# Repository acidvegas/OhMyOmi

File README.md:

# OhMyOmi

A DIY approach to building your own [Omi](https://www.omi.me) wearable for less than the cost of buying one. It is a small round pendant that records your conversations with two MEMS microphones, saves them to on-board flash and syncs to your phone over Bluetooth later, or streams live. The whole board is generated from Python scripts, autorouted with Freerouting and ready to order from JLCPCB with assembly.

| Parts side *(faces into the case)* | Front face *(against the case front)* |
| :---: | :---: |
|  |  |

## Board

- Ø26 mm round, 6 layers, 0.8 mm thick, ENIG
- Every assembled part on one side *(JLCPCB Economic PCBA)*. The blank side sits flat against the inside of the case front.
- Mics listen through 0.8 mm holes in the board and the RGB LED shines through a slot, so no light pipe is needed
- Pendant size with a case is about Ø28.9 x 12.3 mm

| Part                | What it does                                                 |
|---------------------|--------------------------------------------------------------|
| ISP1807-LR-RS       | nRF52840 Bluetooth module with built-in antenna and crystals |
| 2x IM73D122V01      | Infineon PDM microphones, 73 dB SNR, stereo on one bus       |
| MKDV4GCL-ABB        | 512 MB SLC SD NAND over SPI, power switched by a P-MOSFET    |
| LIS2DW12            | Accelerometer for tap controls and motion wake               |
| MCP73832            | LiPo charger, 66 mA                                          |
| TPS7A0233           | 3.3 V LDO, 25 nA quiescent                                   |
| USBLC6-2P6          | ESD protection on USB                                        |
| HRO TYPE-C-31-M-12  | USB-C for charging and USB data                              |
| MHT151RGBCT         | Reverse mount RGB LED                                        |
| DMG1012T + RB521S30 | Vibration motor driver                                       |

The battery is a 150 mAh CP1654 cell with wire leads soldered to the B+ and B- pads. A coin vibration motor solders to M+ and M-. Four test pads on the front face carry SWDIO, SWDCLK, 3V3 and GND for programming.

## Ordering

Upload these from `pcb/jlcpcb/` to JLCPCB:

- `omi-gerbers.zip` for the board
- `omi-bom.csv` and `omi-cpl.csv` for assembly

Check the part rotations in the JLCPCB placement preview before paying, especially LED1, both mics, U4, U5, U6, Q1, Q2, D1 and J1. Cost for 5 boards with 2 assembled is about $120 before shipping, the battery and the motor. The ISP1807 comes through JLCPCB Global Sourcing.

## Firmware notes

The firmware is not written yet. The board depends on these settings:

- PDM clock 1.280 MHz with ratio 80 *(16 kHz)*. The nRF default of 1.032 MHz falls between the mic's power modes and will not work.
- Stereo PDM, MK1 on the falling edge and MK2 on the rising edge
- LED pins P0.13, P0.17 and P0.14 in high drive mode
- Drive P0.30 low to power the SD NAND, and float its SPI pins before turning it off
- Charge status on P0.31 *(low while charging)*
- Battery voltage on AIN4 through a 1M/1M divider, TACQ 40 us
- Enable the nRF DC/DC *(DCDCEN)*
- Compress audio before saving *(Opus)*. Raw 16 kHz stereo fills 512 MB in about 2 hours.
- Use a watchdog. There is no reset button.

## Building

Needs KiCad 9 *(pcbnew Python and kicad-cli)* and Flask for the preview.

```
cd pcb
python3 gen_lib.py                         # footprints, symbols, schematic
python3 build_pcb.py place                 # unrouted board with zones and keepouts
cp omi.kicad_pcb omi_unrouted.kicad_pcb
./flow.sh                                  # autoroute, import, pours, fixups, DRC
./rebuild.sh                               # redo pours, fixups and DRC on the last route without re-routing
python3 outputs.py                         # gerbers, BOM, CPL, renders, 3D model
python3 compare.py                         # size comparison render
python3 summary.py                         # prices, stock and cost for the preview
```

`flow.sh` runs Freerouting 2.5.0 from `tools/` with its own Java 25 runtime, inside `sudo unshare -n` so it has no network access. `tools/` is not tracked. Put `freerouting-2.5.0.jar` and a Java 25 JRE back there to re-route.

## Previews

- `pcb/preview/app.py` serves the board preview *(layers, cost, parts, 3D view at `/3d`)* on port 20005
- `app.py` serves the original dev-board wiring preview on port 20004

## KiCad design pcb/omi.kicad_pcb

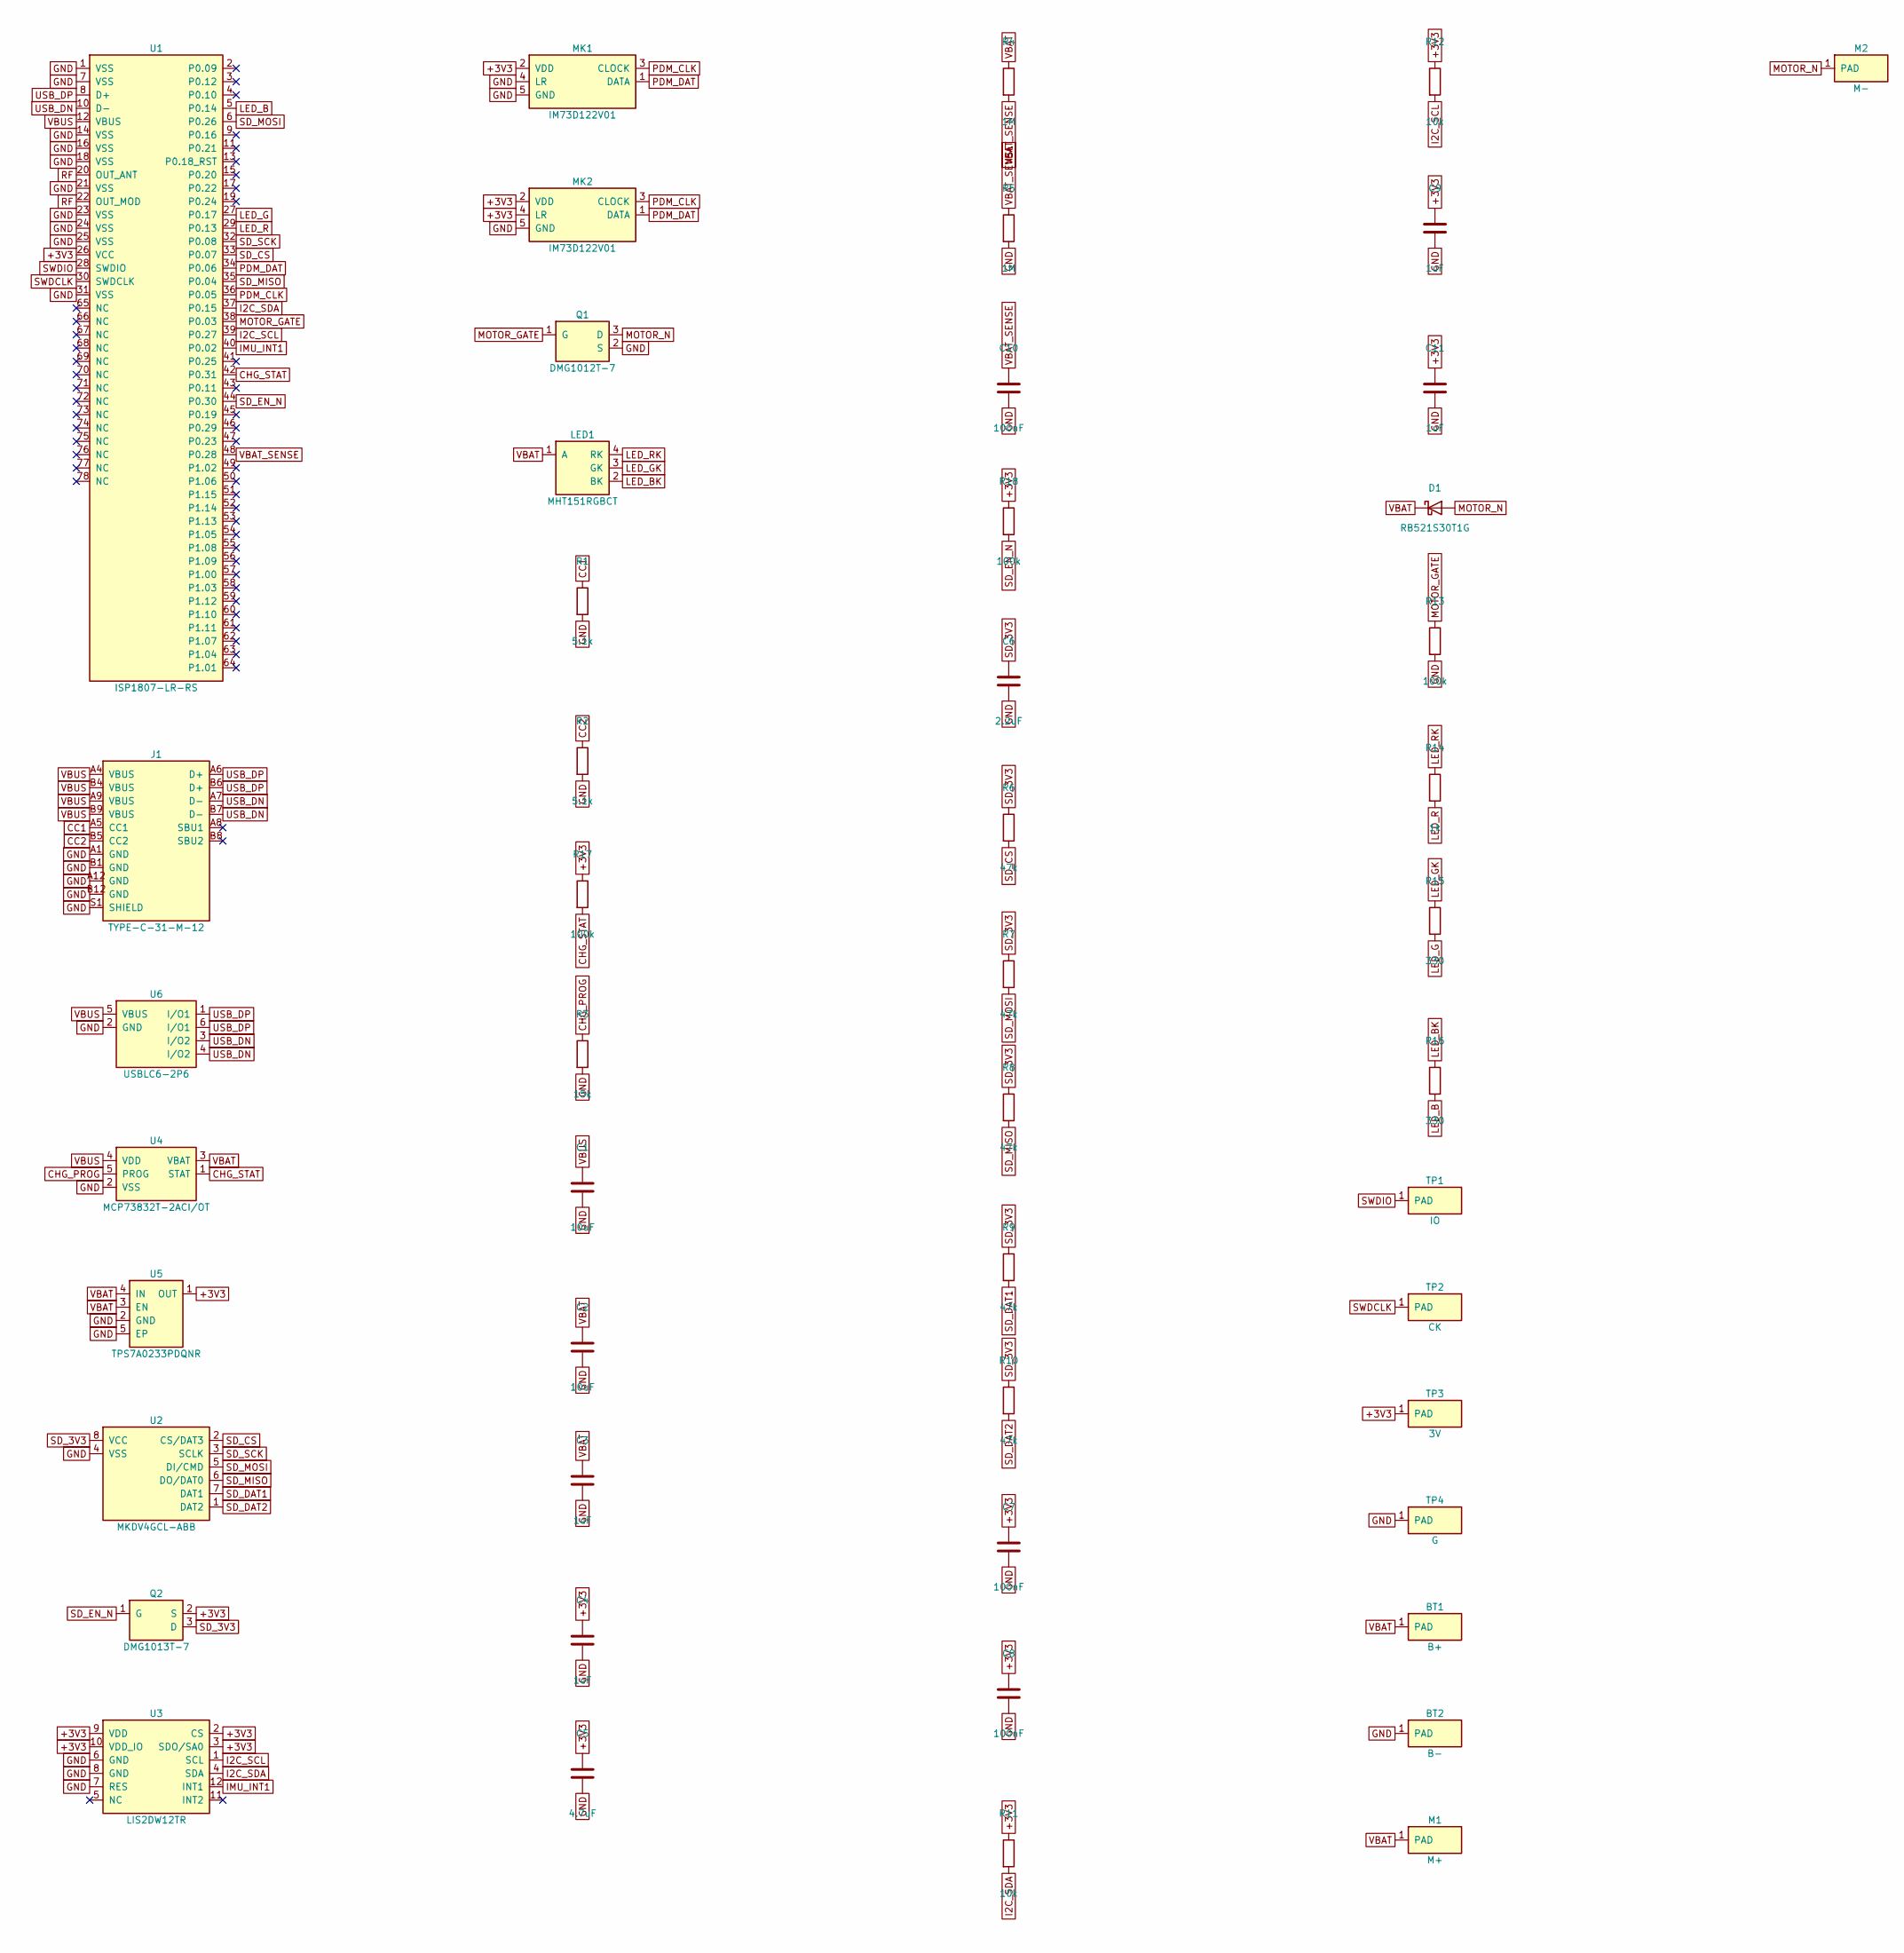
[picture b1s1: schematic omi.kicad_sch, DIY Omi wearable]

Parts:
BT1: B+; TestPoint_Pad_1.0x1.0mm
BT2: B-; TestPoint_Pad_1.0x1.0mm
C1: 10uF; C_0603_1608Metric; LCSC C19702
C2: 10uF; C_0402_1005Metric; LCSC C15525
C3, C4, C9, C11: 1uF; C_0402_1005Metric; LCSC C52923
C5: 4.7uF; C_0402_1005Metric; LCSC C23733
C6: 2.2uF; C_0402_1005Metric; LCSC C12530
C7, C8, C10: 100nF; C_0402_1005Metric; LCSC C1525
D1: RB521S30T1G; D_SOD-523; LCSC C145179
J1: TYPE-C-31-M-12; USB_C_Receptacle_HRO_TYPE-C-31-M-12; LCSC C165948
LED1: MHT151RGBCT; LED_RGB_REV_1206; LCSC C409782
M1: M+; TestPoint_Pad_1.0x1.0mm
M2: M-; TestPoint_Pad_1.0x1.0mm
MK1, MK2: IM73D122V01; IM73D122_LGA5_4x3; LCSC C5563886
Q1: DMG1012T-7; SOT-523; LCSC C20512
Q2: DMG1013T-7; SOT-523; LCSC C96676
R1, R2: 5.1k; R_0402_1005Metric; LCSC C25905
R3: 15k; R_0402_1005Metric; LCSC C25756
R4, R5: 1M; R_0402_1005Metric; LCSC C26083
R6, R7, R8, R9, R10: 47k; R_0402_1005Metric; LCSC C25792
R11, R12: 10k; R_0402_1005Metric; LCSC C25744
R13, R17, R18: 100k; R_0402_1005Metric; LCSC C25741
R14: 1k; R_0402_1005Metric; LCSC C11702
R15, R16: 330; R_0402_1005Metric; LCSC C25104
TP1: IO; TestPoint_Pad_D1.0mm
TP2: CK; TestPoint_Pad_D1.0mm
TP3: 3V; TestPoint_Pad_D1.0mm
TP4: G; TestPoint_Pad_D1.0mm
U1: ISP1807-LR-RS; ISP1807; LCSC C5264268
U2: MKDV4GCL-ABB; SDNAND_LGA8_8x6; LCSC C7500178
U3: LIS2DW12TR; LGA-12_2x2mm_P0.5mm; LCSC C189624
U4: MCP73832T-2ACI/OT; SOT-23-5; LCSC C38066
U5: TPS7A0233PDQNR; Texas_X2SON-4_1x1mm_P0.65mm; LCSC C2860046
U6: USBLC6-2P6; SOT-666; LCSC C15999

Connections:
+3V3: C4.1, C5.1, C7.1, C8.1, C9.1, C11.1, MK1.2 (VDD), MK2.2 (VDD), MK2.4 (LR), Q2.2 (S), R11.1, R12.1, R17.1, R18.1, TP3.1, U1.26 (VCC), U3.2 (CS), U3.3 (SDO/SA0), U3.9 (VDD), U3.10 (VDD_IO), U5.1 (OUT)
CC1: J1.A5 (CC1), R1.1
CC2: J1.B5 (CC2), R2.1
CHG_PROG: R3.1, U4.5 (PROG)
CHG_STAT: R17.2, U1.42 (P0.31), U4.1 (STAT)
GND: BT2.1, C1.2, C2.2, C3.2, C4.2, C5.2, C6.2, C7.2, C8.2, C9.2, C10.2, C11.2, J1.A1 (GND), J1.A12 (GND), J1.B1 (GND), J1.B12 (GND), J1.S1 (SHIELD), MK1.4 (LR), MK1.5 (GND), MK2.5 (GND), Q1.2 (S), R1.2, R2.2, R3.2, R5.2, R13.2, TP4.1, U1.1 (VSS), U1.7 (VSS), U1.14 (VSS), U1.16 (VSS), U1.18 (VSS), U1.21 (VSS), U1.23 (VSS), U1.24 (VSS), U1.25 (VSS), U1.31 (VSS), U2.4 (VSS), U3.6 (GND), U3.7 (RES), U3.8 (GND), U4.2 (VSS), U5.2 (GND), U5.5 (EP), U6.2 (GND)
I2C_SCL: R12.2, U1.39 (P0.27), U3.1 (SCL)
I2C_SDA: R11.2, U1.37 (P0.15), U3.4 (SDA)
IMU_INT1: U1.40 (P0.02), U3.12 (INT1)
LED_B: R16.2, U1.5 (P0.14)
LED_BK: LED1.2 (BK), R16.1
LED_G: R15.2, U1.27 (P0.17)
LED_GK: LED1.3 (GK), R15.1
LED_R: R14.2, U1.29 (P0.13)
LED_RK: LED1.4 (RK), R14.1
MOTOR_GATE: Q1.1 (G), R13.1, U1.38 (P0.03)
MOTOR_N: D1.2 (A), M2.1, Q1.3 (D)
PDM_CLK: MK1.3 (CLOCK), MK2.3 (CLOCK), U1.36 (P0.05)
PDM_DAT: MK1.1 (DATA), MK2.1 (DATA), U1.34 (P0.06)
RF: U1.20 (OUT_ANT), U1.22 (OUT_MOD)
SD_3V3: C6.1, Q2.3 (D), R6.1, R7.1, R8.1, R9.1, R10.1, U2.8 (VCC)
SD_CS: R6.2, U1.33 (P0.07), U2.2 (CS/DAT3)
SD_DAT1: R9.2, U2.7 (DAT1)
SD_DAT2: R10.2, U2.1 (DAT2)
SD_EN_N: Q2.1 (G), R18.2, U1.44 (P0.30)
SD_MISO: R8.2, U1.35 (P0.04), U2.6 (DO/DAT0)
SD_MOSI: R7.2, U1.6 (P0.26), U2.5 (DI/CMD)
SD_SCK: U1.32 (P0.08), U2.3 (SCLK)
SWDCLK: TP2.1, U1.30 (SWDCLK)
SWDIO: TP1.1, U1.28 (SWDIO)
USB_DN: J1.A7 (D-), J1.B7 (D-), U1.10 (D-), U6.3 (I/O2), U6.4 (I/O2)
USB_DP: J1.A6 (D+), J1.B6 (D+), U1.8 (D+), U6.1 (I/O1), U6.6 (I/O1)
VBAT: BT1.1, C2.1, C3.1, D1.1 (K), LED1.1 (A), M1.1, R4.1, U4.3 (VBAT), U5.3 (EN), U5.4 (IN)
VBAT_SENSE: C10.1, R4.2, R5.1, U1.48 (P0.28)
VBUS: C1.1, J1.A4 (VBUS), J1.A9 (VBUS), J1.B4 (VBUS), J1.B9 (VBUS), U1.12 (VBUS), U4.4 (VDD), U6.5 (VBUS)

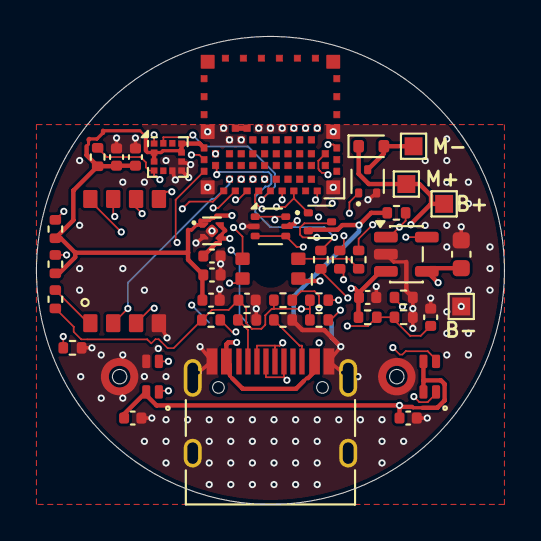
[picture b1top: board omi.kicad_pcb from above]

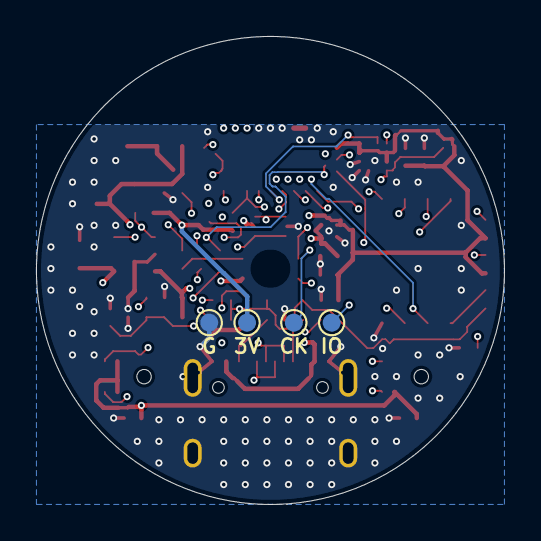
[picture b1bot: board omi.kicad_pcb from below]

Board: 6 copper layers, 26.0 x 26.0 mm, 50 parts (4 on the bottom side), 35 nets.

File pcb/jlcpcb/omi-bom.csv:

Comment,Designator,Footprint,LCSC Part #
ISP1807-LR-RS,U1,ISP1807,C5264268
TYPE-C-31-M-12,J1,USB_C_Receptacle_HRO_TYPE-C-31-M-12,C165948
5.1k,"R1,R2",R_0402_1005Metric,C25905
USBLC6-2P6,U6,SOT-666,C15999
MCP73832T-2ACI/OT,U4,SOT-23-5,C38066
100k,"R17,R18,R13",R_0402_1005Metric,C25741
15k,R3,R_0402_1005Metric,C25756
10uF,C1,C_0603_1608Metric,C19702
10uF,C2,C_0402_1005Metric,C15525
TPS7A0233PDQNR,U5,Texas_X2SON-4_1x1mm_P0.65mm,C2860046
1uF,"C3,C4,C9,C11",C_0402_1005Metric,C52923
4.7uF,C5,C_0402_1005Metric,C23733
1M,"R4,R5",R_0402_1005Metric,C26083
100nF,"C10,C7,C8",C_0402_1005Metric,C1525
MKDV4GCL-ABB,U2,SDNAND_LGA8_8x6,C7500178
DMG1013T-7,Q2,SOT-523,C96676
2.2uF,C6,C_0402_1005Metric,C12530
47k,"R6,R7,R8,R9,R10",R_0402_1005Metric,C25792
LIS2DW12TR,U3,LGA-12_2x2mm_P0.5mm,C189624
10k,"R11,R12",R_0402_1005Metric,C25744
IM73D122V01,"MK1,MK2",IM73D122_LGA5_4x3,C5563886
DMG1012T-7,Q1,SOT-523,C20512
RB521S30T1G,D1,D_SOD-523,C145179
MHT151RGBCT,LED1,LED_RGB_REV_1206,C409782
1k,R14,R_0402_1005Metric,C11702
330,"R15,R16",R_0402_1005Metric,C25104

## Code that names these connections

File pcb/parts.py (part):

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		'32': 'SD_SCK', '6': 'SD_MOSI', '35': 'SD_MISO', '33': 'SD_CS',
		'37': 'I2C_SDA', '39': 'I2C_SCL', '40': 'IMU_INT1',
		'48': 'VBAT_SENSE', '38': 'MOTOR_GATE',
		'29': 'LED_R', '27': 'LED_G', '5': 'LED_B',  # high-drive capable pins (P0.13/P0.17/P0.14)
		'42': 'CHG_STAT', '44': 'SD_EN_N',  # static signals on low-frequency pins (P0.31/P0.30)
	}),

	# --- USB-C charging/data at the bottom edge, 5.1k CC pull-downs so any USB-C charger supplies 5V ---
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	dict(ref='R1', value='5.1k', sym='Device:R', fp='Resistor_SMD:R_0402_1005Metric', lcsc='C25905', pins={'1': 'CC1', '2': 'GND'}),
	dict(ref='R2', value='5.1k', sym='Device:R', fp='Resistor_SMD:R_0402_1005Metric', lcsc='C25905', pins={'1': 'CC2', '2': 'GND'}),
	# ESD clamp on D+/D-/VBUS (flow-through: pins 1/6 = I/O1, 3/4 = I/O2)
	dict(ref='U6', value='USBLC6-2P6', sym='omi:USBLC6', fp='Package_TO_SOT_SMD:SOT-666', lcsc='C15999', pins={'1': 'USB_DP', '6': 'USB_DP', '3': 'USB_DN', '4': 'USB_DN', '2': 'GND', '5': 'VBUS'}),

	# --- charger: MCP73832 (open-drain STAT), I = 1000V / RPROG -> 15k = 66mA (~0.5C for a 120-150mAh CP1654 cell) ---
	dict(ref='U4', value='MCP73832T-2ACI/OT', sym='omi:MCP73832', fp='Package_TO_SOT_SMD:SOT-23-5', lcsc='C38066', pins={'1': 'CHG_STAT', '2': 'GND', '3': 'VBAT', '4': 'VBUS', '5': 'CHG_PROG'}),
	dict(ref='R17', value='100k', sym='Device:R', fp='Resistor_SMD:R_0402_1005Metric', lcsc='C25741', pins={'1': '+3V3', '2': 'CHG_STAT'}),
	dict(ref='R3', value='15k', sym='Device:R', fp='Resistor_SMD:R_0402_1005Metric', lcsc='C25756', pins={'1': 'CHG_PROG', '2': 'GND'}),
	dict(ref='C1', value='10uF', sym='Device:C', fp='Capacitor_SMD:C_0603_1608Metric', lcsc='C19702', pins={'1': 'VBUS', '2': 'GND'}),
	dict(ref='C2', value='10uF', sym='Device:C', fp='Capacitor_SMD:C_0402_1005Metric', lcsc='C15525', pins={'1': 'VBAT', '2': 'GND'}),

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	dict(ref='C5', value='4.7uF', sym='Device:C', fp='Capacitor_SMD:C_0402_1005Metric', lcsc='C23733', pins={'1': '+3V3', '2': 'GND'}),

	# --- battery sense divider (VBAT/2 on P0.28 = AIN4, sample with TACQ = 40 us) ---
	dict(ref='R4', value='1M', sym='Device:R', fp='Resistor_SMD:R_0402_1005Metric', lcsc='C26083', pins={'1': 'VBAT', '2': 'VBAT_SENSE'}),
	dict(ref='R5', value='1M', sym='Device:R', fp='Resistor_SMD:R_0402_1005Metric', lcsc='C26083', pins={'1': 'VBAT_SENSE', '2': 'GND'}),
	dict(ref='C10', value='100nF', sym='Device:C', fp='Capacitor_SMD:C_0402_1005Metric', lcsc='C1525', pins={'1': 'VBAT_SENSE', '2': 'GND'}),

	# --- SD NAND 4 Gbit / 512 MB (SPI mode), on its own switched rail so standby drops ~50 uA -> 0 ---
	dict(ref='U2', value='MKDV4GCL-ABB', sym='omi:SDNAND', fp='omi:SDNAND_LGA8_8x6', lcsc='C7500178', pins={'1': 'SD_DAT2', '2': 'SD_CS', '3': 'SD_SCK', '4': 'GND', '5': 'SD_MOSI', '6': 'SD_MISO', '7': 'SD_DAT1', '8': 'SD_3V3'}),
	dict(ref='Q2', value='DMG1013T-7', sym='omi:PMOS_GSD', fp='Package_TO_SOT_SMD:SOT-523', lcsc='C96676', pins={'1': 'SD_EN_N', '2': '+3V3', '3': 'SD_3V3'}),
	dict(ref='R18', value='100k', sym='Device:R', fp='Resistor_SMD:R_0402_1005Metric', lcsc='C25741', pins={'1': '+3V3', '2': 'SD_EN_N'}),
	dict(ref='C6', value='2.2uF', sym='Device:C', fp='Capacitor_SMD:C_0402_1005Metric', lcsc='C12530', pins={'1': 'SD_3V3', '2': 'GND'}),
	dict(ref='R6', value='47k', sym='Device:R', fp='Resistor_SMD:R_0402_1005Metric', lcsc='C25792', pins={'1': 'SD_3V3', '2': 'SD_CS'}),
	dict(ref='R7', value='47k', sym='Device:R', fp='Resistor_SMD:R_0402_1005Metric', lcsc='C25792', pins={'1': 'SD_3V3', '2': 'SD_MOSI'}),
	dict(ref='R8', value='47k', sym='Device:R', fp='Resistor_SMD:R_0402_1005Metric', lcsc='C25792', pins={'1': 'SD_3V3', '2': 'SD_MISO'}),
	dict(ref='R9', value='47k', sym='Device:R', fp='Resistor_SMD:R_0402_1005Metric', lcsc='C25792', pins={'1': 'SD_3V3', '2': 'SD_DAT1'}),
	dict(ref='R10', value='47k', sym='Device:R', fp='Resistor_SMD:R_0402_1005Metric', lcsc='C25792', pins={'1': 'SD_3V3', '2': 'SD_DAT2'}),

	# --- accelerometer for motion wake (I2C, CS and SA0 tied high so their internal pull-ups draw nothing, addr 0x19) ---
	dict(ref='U3', value='LIS2DW12TR', sym='omi:LIS2DW12', fp='Package_LGA:LGA-12_2x2mm_P0.5mm', lcsc='C189624', pins={
		'1': 'I2C_SCL', '2': '+3V3', '3': '+3V3', '4': 'I2C_SDA', '5': None, '6': 'GND', '7': 'GND', '8': 'GND', '9': '+3V3', '10': '+3V3', '11': None, '12': 'IMU_INT1'}),
	dict(ref='C7', value='100nF', sym='Device:C', fp='Capacitor_SMD:C_0402_1005Metric', lcsc='C1525', pins={'1': '+3V3', '2': 'GND'}),
	dict(ref='C8', value='100nF', sym='Device:C', fp='Capacitor_SMD:C_0402_1005Metric', lcsc='C1525', pins={'1': '+3V3', '2': 'GND'}),
	dict(ref='R11', value='10k', sym='Device:R', fp='Resistor_SMD:R_0402_1005Metric', lcsc='C25744', pins={'1': '+3V3', '2': 'I2C_SDA'}),
	dict(ref='R12', value='10k', sym='Device:R', fp='Resistor_SMD:R_0402_1005Metric', lcsc='C25744', pins={'1': '+3V3', '2': 'I2C_SCL'}),

	# --- 2x bottom-port PDM mics on the component side, listening through 0.8 mm board holes straight out the front face; shared clock/data, LR selects the edge ---
	dict(ref='MK1', value='IM73D122V01', sym='omi:IM73D122', fp='omi:IM73D122_LGA5_4x3', lcsc='C5563886', pins={'1': 'PDM_DAT', '2': '+3V3', '3': 'PDM_CLK', '4': 'GND', '5': 'GND'}),
	dict(ref='MK2', value='IM73D122V01', sym='omi:IM73D122', fp='omi:IM73D122_LGA5_4x3', lcsc='C5563886', pins={'1': 'PDM_DAT', '2': '+3V3', '3': 'PDM_CLK', '4': '+3V3', '5': 'GND'}),
	dict(ref='C9', value='1uF', sym='Device:C', fp='Capacitor_SMD:C_0402_1005Metric', lcsc='C52923', pins={'1': '+3V3', '2': 'GND'}),
	dict(ref='C11', value='1uF', sym='Device:C', fp='Capacitor_SMD:C_0402_1005Metric', lcsc='C52923', pins={'1': '+3V3', '2': 'GND'}),

	# --- vibration motor driver (motor solders to M+ / M- pads) ---
	dict(ref='Q1', value='DMG1012T-7', sym='omi:NMOS_GSD', fp='Package_TO_SOT_SMD:SOT-523', lcsc='C20512', pins={'1': 'MOTOR_GATE', '2': 'GND', '3': 'MOTOR_N'}),
	dict(ref='D1', value='RB521S30T1G', sym='Device:D_Schottky', fp='Diode_SMD:D_SOD-523', lcsc='C145179', pins={'1': 'VBAT', '2': 'MOTOR_N'}),
	dict(ref='R13', value='100k', sym='Device:R', fp='Resistor_SMD:R_0402_1005Metric', lcsc='C25741', pins={'1': 'MOTOR_GATE', '2': 'GND'}),

	# --- RGB LED, reverse mount: sits on the inner side and shines out through a slot in the board (common anode on VBAT, GPIO sinks) ---
	dict(ref='LED1', value='MHT151RGBCT', sym='omi:LED_RGB_CA', fp='omi:LED_RGB_REV_1206', lcsc='C409782', pins={'1': 'VBAT', '2': 'LED_BK', '3': 'LED_GK', '4': 'LED_RK'}),
	dict(ref='R14', value='1k', sym='Device:R', fp='Resistor_SMD:R_0402_1005Metric', lcsc='C11702', pins={'1': 'LED_RK', '2': 'LED_R'}),
	dict(ref='R15', value='330', sym='Device:R', fp='Resistor_SMD:R_0402_1005Metric', lcsc='C25104', pins={'1': 'LED_GK', '2': 'LED_G'}),
	dict(ref='R16', value='330', sym='Device:R', fp='Resistor_SMD:R_0402_1005Metric', lcsc='C25104', pins={'1': 'LED_BK', '2': 'LED_B'}),

	# --- solder pads (not assembled): SWD test pads on the blank front face, battery and motor wire pads on the component side ---
	dict(ref='TP1', value='IO', sym='omi:PAD', fp='TestPoint:TestPoint_Pad_D1.0mm', lcsc=None, side='B', pins={'1': 'SWDIO'}),
	dict(ref='TP2', value='CK', sym='omi:PAD', fp='TestPoint:TestPoint_Pad_D1.0mm', lcsc=None, side='B', pins={'1': 'SWDCLK'}),
	dict(ref='TP3', value='3V', sym='omi:PAD', fp='TestPoint:TestPoint_Pad_D1.0mm', lcsc=None, side='B', pins={'1': '+3V3'}),
	dict(ref='TP4', value='G', sym='omi:PAD', fp='TestPoint:TestPoint_Pad_D1.0mm', lcsc=None, side='B', pins={'1': 'GND'}),
	dict(ref='BT1', value='B+', sym='omi:PAD', fp='TestPoint:TestPoint_Pad_1.0x1.0mm', lcsc=None, pins={'1': 'VBAT'}),
	dict(ref='BT2', value='B-', sym='omi:PAD', fp='TestPoint:TestPoint_Pad_1.0x1.0mm', lcsc=None, pins={'1': 'GND'}),
	dict(ref='M1', value='M+', sym='omi:PAD', fp='TestPoint:TestPoint_Pad_1.0x1.0mm', lcsc=None, pins={'1': 'VBAT'}),
	dict(ref='M2', value='M-', sym='omi:PAD', fp='TestPoint:TestPoint_Pad_1.0x1.0mm', lcsc=None, pins={'1': 'MOTOR_N'}),
]

# ISP1807 pad table in datasheet top-view coords (mm from top-left corner): num -> (x, y, w, h)
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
